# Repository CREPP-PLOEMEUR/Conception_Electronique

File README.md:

# Conception_Electronique
Le répertoire avec les sources de l'atelier Conception Electronique

## Installation de Kicad

La version de Kicad sera la version 8.X : 

## Projets 2024-2025

Pour cette année, les projets souhaités sont :

- Une station météo
- Une carte de développement pour microcontrôleur 

- Cahier des charges
- Schématique
- Commande de matériel
- Affectation des empreintes
- Routage
- Génération du dossier de fabrication
- Montage
- Debug

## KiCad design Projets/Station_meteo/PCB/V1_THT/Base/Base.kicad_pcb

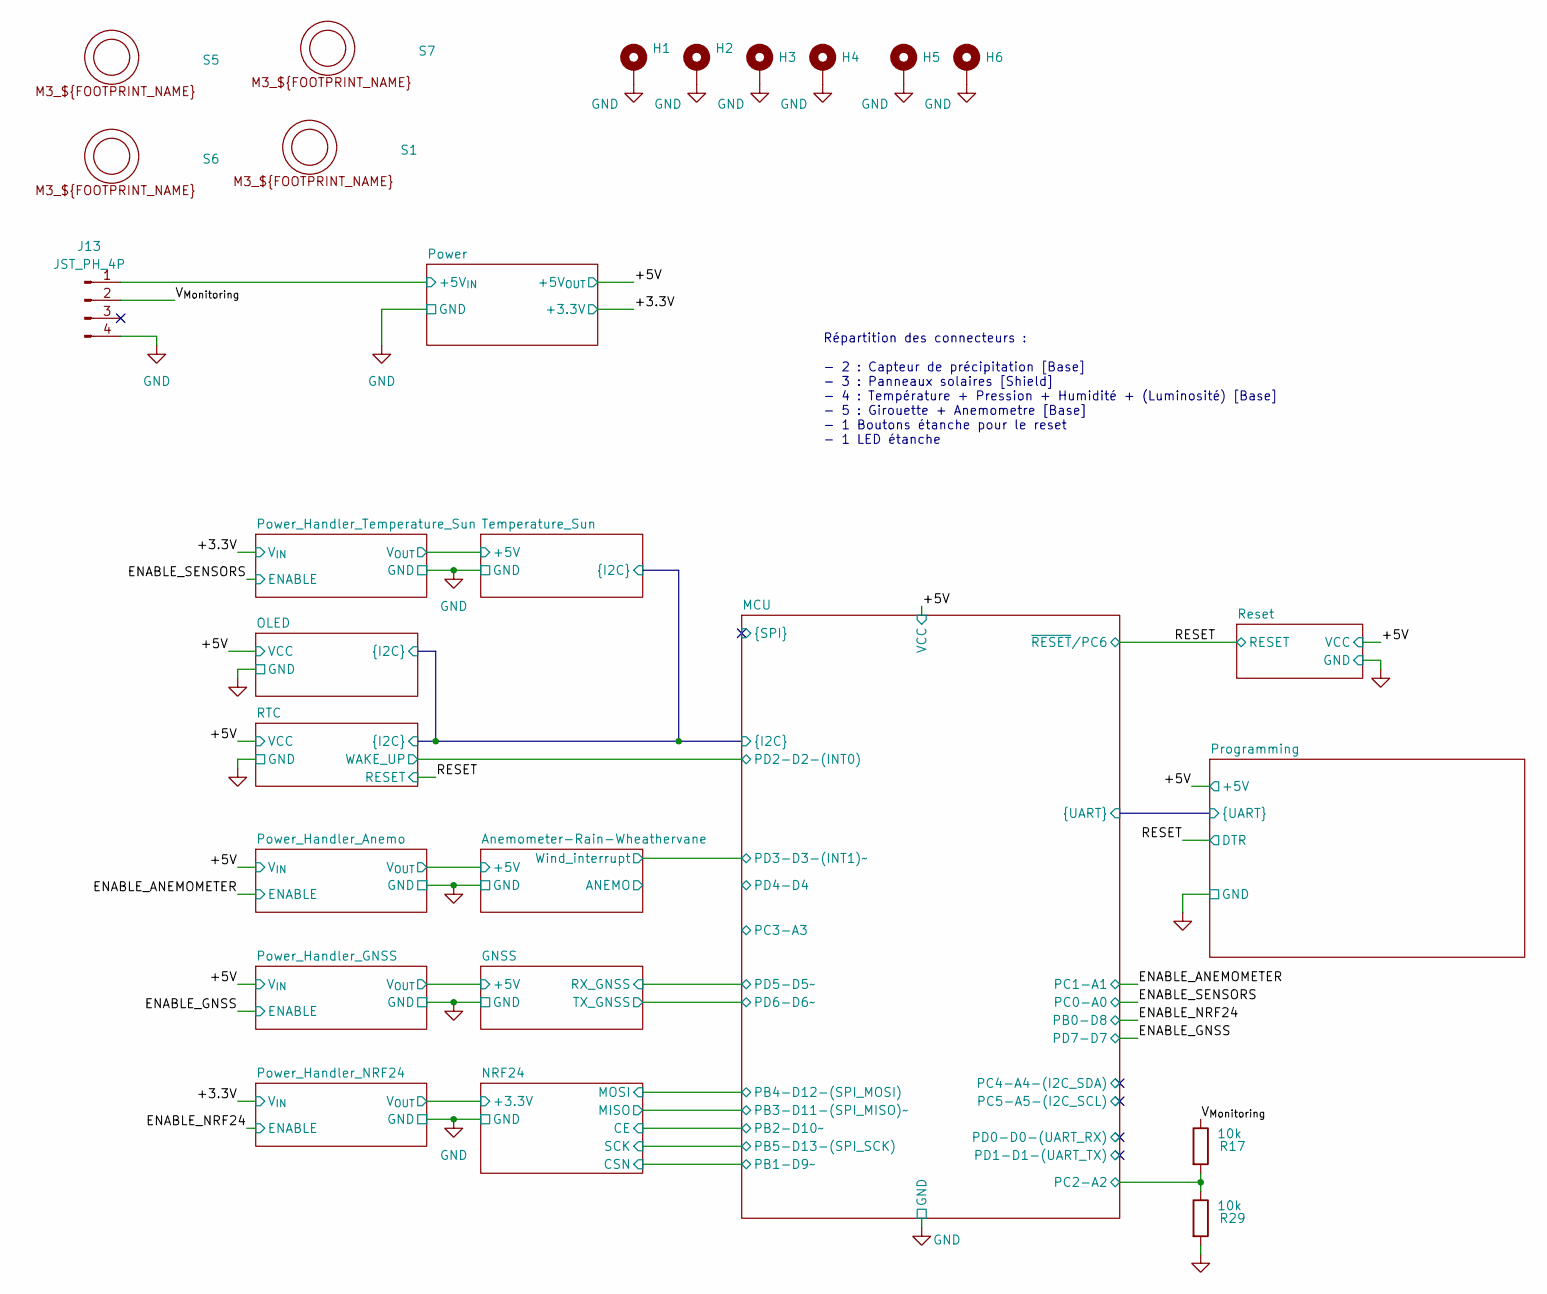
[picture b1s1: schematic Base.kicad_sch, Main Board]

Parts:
H1, H2, H3, H4, H5, H6: MountingHole_Pad; MountingHole_3.2mm_M3
J13: JST_PH_4P; JST_PH_B4B-PH-K_1x04_P2.00mm_Vertical
R17, R29: 10k; R_Axial_DIN0207_L6.3mm_D2.5mm_P7.62mm_Horizontal
S1, S5, S6, S7: Spacer_M3_MF_05mm

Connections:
/MCU/PC2-A2: R17.2, R29.1; also elsewhere on the board
/Power/+5V_{IN}: J13.1; also elsewhere on the board
/V_{Monitoring}: J13.2, R17.1
GND: H1.1, H2.1, H3.1, H4.1, H5.1, H6.1, J13.4, R29.2; also elsewhere on the board

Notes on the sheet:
Répartition des connecteurs : - 2 : Capteur de précipitation [Base] - 3 : Panneaux solaires [Shield] - 4 : Température + Pression + Humidité + (Luminosité) [Base] - 5 : Girouette + Anemometre [Base] - 1 Boutons étanche pour le reset - 1 LED étanche

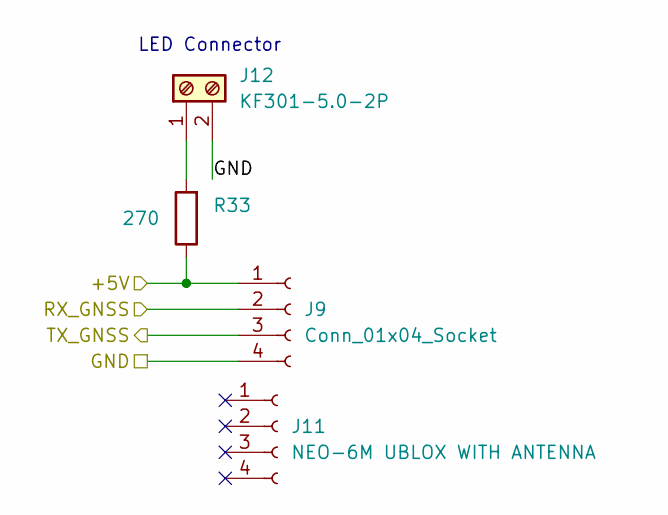
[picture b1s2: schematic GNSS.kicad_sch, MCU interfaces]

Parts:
J9: Conn_01x04_Socket; PinSocket_1x04_P2.54mm_Vertical
J11: NEO-6M UBLOX WITH ANTENNA; PinSocket_1x04_P2.54mm_Vertical
J12: KF301-5.0-2P; TerminalBlock_Phoenix_MKDS-1,5-2_1x02_P5.00mm_Horizontal
R33: 270; R_Axial_DIN0207_L6.3mm_D2.5mm_P7.62mm_Horizontal

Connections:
/GNSS/+5V: J9.1, R33.1; also elsewhere on the board
/GNSS/RX_GNSS: J9.2; also elsewhere on the board
/GNSS/TX_GNSS: J9.3; also elsewhere on the board
GND: J9.4, J12.2; also elsewhere on the board
unnamed: J12.1, R33.2

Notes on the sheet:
LED Connector

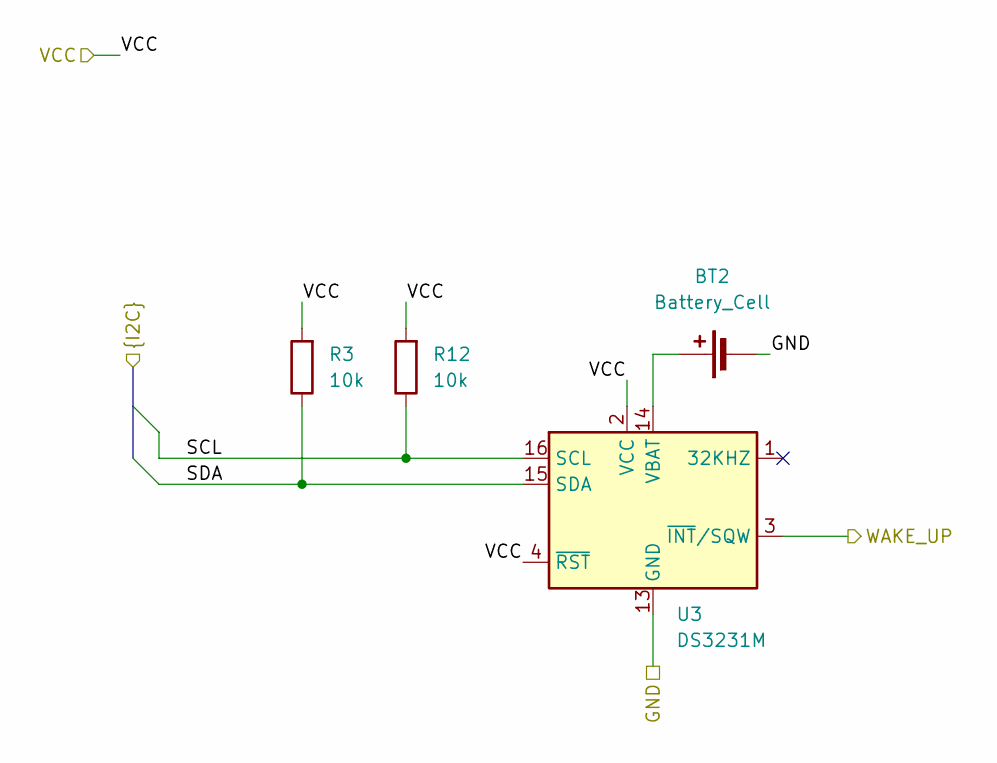
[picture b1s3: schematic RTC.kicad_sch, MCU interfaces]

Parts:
BT2: Battery_Cell; MPD_BC501SM-TR
R3, R12: 10k; R_Axial_DIN0207_L6.3mm_D2.5mm_P7.62mm_Horizontal
U3: DS3231M; SOIC-16W_7.5x10.3mm_P1.27mm

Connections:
/MCU/PD2-D2-(INT0): U3.3 (~INT/SQW); also elsewhere on the board
/MCU/SCL: R12.1, U3.16 (SCL); also elsewhere on the board
/MCU/SDA: R3.1, U3.15 (SDA); also elsewhere on the board
GND: U3.5 (GND), U3.6 (GND), U3.7 (GND), U3.8 (GND), U3.9 (GND), U3.10 (GND), U3.11 (GND), U3.12 (GND), U3.13 (GND); also elsewhere on the board
unnamed: BT2.1 (+), U3.14 (VBAT)
unnamed 75: R3.1; also elsewhere on the board
unnamed 76: R12.1; also elsewhere on the board
unnamed 77: R3.2, R12.2; also elsewhere on the board

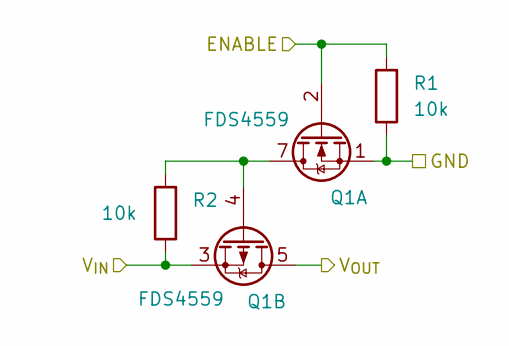
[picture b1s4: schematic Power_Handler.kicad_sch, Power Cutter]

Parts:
Q1: FDS4559; SOIC-8_3.9x4.9mm_P1.27mm
R1, R2: 10k; R_Axial_DIN0207_L6.3mm_D2.5mm_P7.62mm_Horizontal

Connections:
/Anemometer-Rain-Wheathervane/+5V: Q1.5 (D), Q1.6 (D); also elsewhere on the board
/ENABLE_ANEMOMETER: Q1.2 (G), R1.2; also elsewhere on the board
GND: Q1.1 (S), R1.1; also elsewhere on the board
unnamed: Q1.4 (G), Q1.7 (D), Q1.8 (D), R2.2

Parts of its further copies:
Q2, Q3, Q4: FDS4559; SOIC-8_3.9x4.9mm_P1.27mm
R14, R15, R16, R18, R19, R28: 10k; R_Axial_DIN0207_L6.3mm_D2.5mm_P7.62mm_Horizontal

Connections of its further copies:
/+3.3V: Q2.3 (1), Q4.3 (1), R18.1, R28.1; also elsewhere on the board
/ENABLE_GNSS: Q3.2 (G), R15.2; also elsewhere on the board
/ENABLE_NRF24: Q2.2 (G), R14.2; also elsewhere on the board
/ENABLE_SENSORS: Q4.2 (G), R16.2; also elsewhere on the board
/GNSS/+5V: Q3.5 (D), Q3.6 (D); also elsewhere on the board
/NRF24/+3.3V: Q2.5 (D), Q2.6 (D); also elsewhere on the board
/Power_Handler_Temperature_Sun/V_{OUT}: Q4.5 (D), Q4.6 (D)
GND: Q2.1 (S), Q3.1 (S), Q4.1 (S), R14.1, R15.1, R16.1; also elsewhere on the board
unnamed: Q2.4 (G), Q2.7 (D), Q2.8 (D), R18.2
unnamed: Q3.4 (G), Q3.7 (D), Q3.8 (D), R19.2
unnamed: Q4.4 (G), Q4.7 (D), Q4.8 (D), R28.2

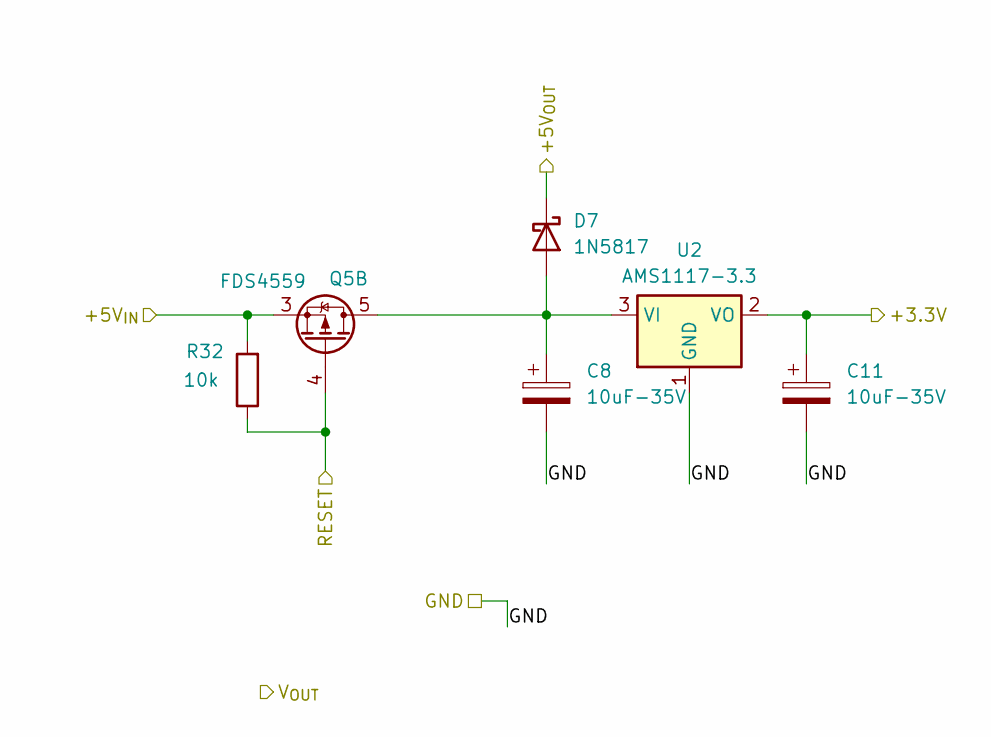
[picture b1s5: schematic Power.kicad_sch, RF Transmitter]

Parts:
C8, C11: 10uF-35V; C_Radial_D5.0mm_H11.0mm_P2.00mm
D7: 1N5817; D_DO-41_SOD81_P10.16mm_Horizontal
Q5: FDS4559; SOIC-8_3.9x4.9mm_P1.27mm
R32: 10k; R_Axial_DIN0207_L6.3mm_D2.5mm_P7.62mm_Horizontal
U2: AMS1117-3.3; SOT-223-3_TabPin2

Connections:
/+3.3V: C11.1, U2.2 (VO); also elsewhere on the board
/Power/+5V_{IN}: Q5.3 (1), R32.2; also elsewhere on the board
/Power/RESET: Q5.4 (G), R32.1
GND: C8.2, C11.2, U2.1 (GND); also elsewhere on the board
unnamed: C8.1, D7.2 (A), Q5.5 (D), Q5.6 (D), U2.3 (VI)

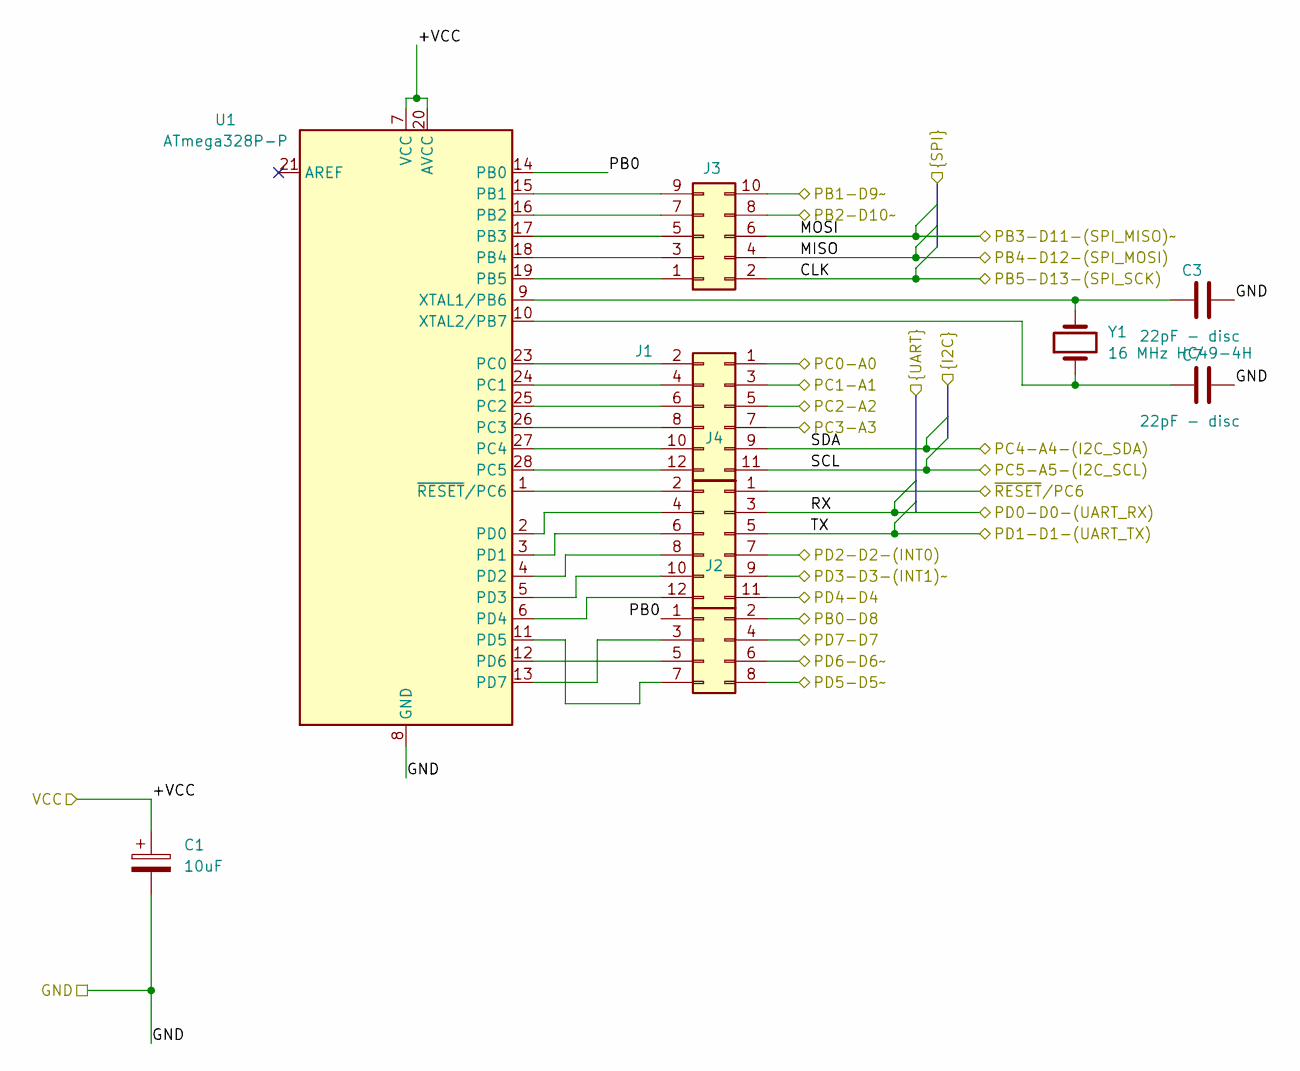
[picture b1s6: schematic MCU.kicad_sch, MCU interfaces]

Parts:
C1: 10uF; C_Radial_D5.0mm_H11.0mm_P2.00mm
C3, C7: 22pF - disc; C_Disc_D4.3mm_W1.9mm_P5.00mm
J1: Conn_02x05_Odd_Even; PinHeader_2x05_P2.54mm_Vertical
J2: Conn_02x04_Odd_Even; PinHeader_2x04_P2.54mm_Vertical
J3, J4: Conn_02x06_Odd_Even; PinHeader_2x06_P2.54mm_Vertical
U1: ATmega328P-P; DIP-28_W7.62mm_Socket
Y1: 16 MHz HC49-4H; Crystal_HC49-4H_Vertical

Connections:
/Anemometer-Rain-Wheathervane/Wind_interrupt: J4.9; also elsewhere on the board
/ENABLE_ANEMOMETER: J3.3; also elsewhere on the board
/ENABLE_GNSS: J2.4; also elsewhere on the board
/ENABLE_NRF24: J2.2; also elsewhere on the board
/ENABLE_SENSORS: J3.1; also elsewhere on the board
/GNSS/RX_GNSS: J2.8; also elsewhere on the board
/GNSS/TX_GNSS: J2.6; also elsewhere on the board
/MCU/CLK: J1.2; also elsewhere on the board
/MCU/MISO: J1.4; also elsewhere on the board
/MCU/MOSI: J1.6; also elsewhere on the board
/MCU/PB0: J2.1, U1.14 (PB0)
/MCU/PB1-D9~: J1.10; also elsewhere on the board
/MCU/PB2-D10~: J1.8; also elsewhere on the board
/MCU/PC2-A2: J3.5; also elsewhere on the board
/MCU/PC3-A3: J3.7
/MCU/PD2-D2-(INT0): J4.7; also elsewhere on the board
/MCU/PD4-D4: J4.11
/MCU/RX: J4.3; also elsewhere on the board
/MCU/SCL: J3.11; also elsewhere on the board
/MCU/SDA: J3.9; also elsewhere on the board
/MCU/TX: J4.5; also elsewhere on the board
GND: C1.2, C3.2, C7.2, U1.8 (GND), U1.22 (GND); also elsewhere on the board
unnamed: J1.1, U1.19 (PB5)
unnamed: J1.3, U1.18 (PB4)
unnamed: J1.5, U1.17 (PB3)
unnamed: J1.7, U1.16 (PB2)
unnamed: J1.9, U1.15 (PB1)
unnamed: J2.3, U1.13 (PD7)
unnamed: J2.5, U1.12 (PD6)
unnamed: J2.7, U1.11 (PD5)
unnamed: J3.2, U1.23 (PC0)
unnamed: J3.4, U1.24 (PC1)
unnamed: J3.6, U1.25 (PC2)
unnamed: J3.8, U1.26 (PC3)
unnamed: J3.10, U1.27 (PC4)
unnamed: J3.12, U1.28 (PC5)
unnamed: J4.2, U1.1 (~RESET/PC6)
unnamed: J4.4, U1.2 (PD0)
unnamed: J4.6, U1.3 (PD1)
unnamed: J4.8, U1.4 (PD2)
unnamed: J4.10, U1.5 (PD3)
unnamed: J4.12, U1.6 (PD4)
unnamed: C3.1, U1.9 (XTAL1/PB6), Y1.2
unnamed: C7.1, U1.10 (XTAL2/PB7), Y1.1

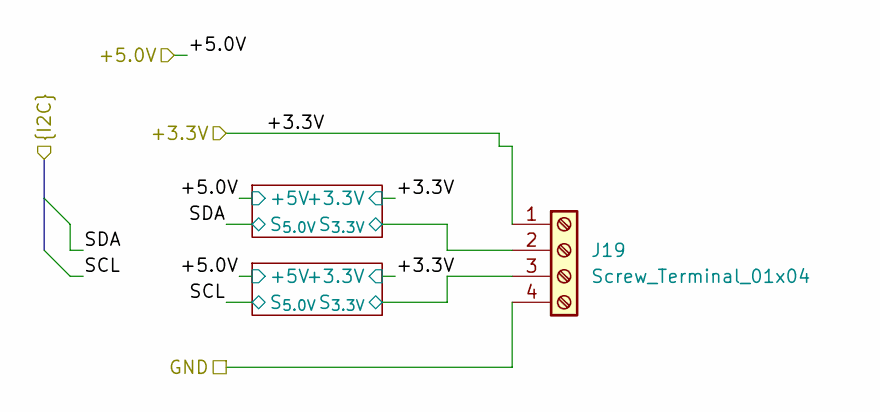
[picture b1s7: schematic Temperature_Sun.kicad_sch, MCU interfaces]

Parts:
J19: Screw_Terminal_01x04; TerminalBlock_Phoenix_MKDS-1,5-4-5.08_1x04_P5.08mm_Horizont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

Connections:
/Temperature_Sun/+3.3V: J19.1; also elsewhere on the board
/Temperature_Sun/Translator1/S_{3.3V}: J19.3; also elsewhere on the board
/Temperature_Sun/Translator/S_{3.3V}: J19.2; also elsewhere on the board
GND: J19.4; also elsewhere on the board

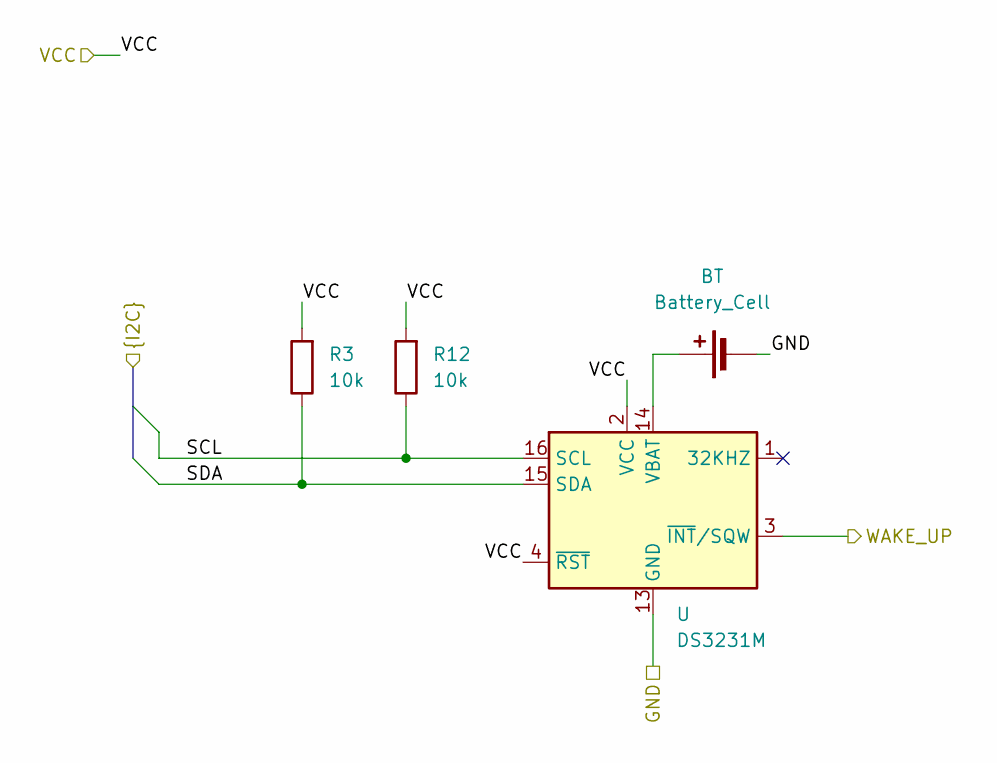
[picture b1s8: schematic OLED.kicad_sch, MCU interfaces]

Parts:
BT: Battery_Cell; MPD_BC501SM-TR
R3, R12: 10k; R_Axial_DIN0207_L6.3mm_D2.5mm_P7.62mm_Horizontal
U: DS3231M; SOIC-16W_7.5x10.3mm_P1.27mm

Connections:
/MCU/SCL: R12.1; also elsewhere on the board
/MCU/SDA: R3.1; also elsewhere on the board
unnamed: BT.1 (+), U.14 (VBAT)
unnamed: R3.1, U.15 (SDA)
unnamed: R12.1, U.16 (SCL)
unnamed: R3.2, R12.2, U.2 (VCC), U.4 (~RST)
unnamed: U.5 (GND), U.6 (GND), U.7 (GND), U.8 (GND), U.9 (GND), U.10 (GND), U.11 (GND), U.12 (GND), U.13 (GND)

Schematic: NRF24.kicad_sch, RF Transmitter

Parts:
U8: NRF24L01_Breakout; nRF24L01_Breakout

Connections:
/MCU/MOSI: U8.7 (MISO); also elsewhere on the board
/NRF24/+3.3V: U8.2 (VCC); also elsewhere on the board
/NRF24/Bridge1/OUT: U8.6 (MOSI); also elsewhere on the board
/NRF24/Bridge2/OUT: U8.4 (~CSN); also elsewhere on the board
/NRF24/Bridge3/OUT: U8.3 (CE); also elsewhere on the board
/NRF24/Bridge/OUT: U8.5 (SCK); also elsewhere on the board
GND: U8.1 (GND); also elsewhere on the board

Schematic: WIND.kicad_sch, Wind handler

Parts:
C4, C6: 100nF; C_0603_1608Metric
C5: 10uF; C_Radial_D5.0mm_H11.0mm_P2.00mm
D1: LED; LED_D3.0mm
D8: 1N5817; D_DO-41_SOD81_P10.16mm_Horizontal
J5: KF301-5.0-2P; TerminalBlock_Phoenix_MKDS-1,5-2_1x02_P5.00mm_Horizontal
J6: Conn_01x03_Pin; PinHeader_1x03_P2.54mm_Vertical
J20: Screw_Terminal_01x04; TerminalBlock_Phoenix_MKDS-1,5-4-5.08_1x04_P5.08mm_Horizont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
JP2: Jumper; PinHeader_1x02_P2.54mm_Vertical
JP3: Jumper_2.54mm_blue
R4: R_10K_SMD_0603; R_0603_1608Metric
R5, R11: 100k; R_Axial_DIN0207_L6.3mm_D2.5mm_P7.62mm_Horizontal
R6, R7, R8, R10: 10k; R_Axial_DIN0207_L6.3mm_D2.5mm_P7.62mm_Horizontal
R9: 270; R_Axial_DIN0207_L6.3mm_D2.5mm_P7.62mm_Horizontal
RV1: R_Potentiometer; Potentiometer_Bourns_3266Y_Vertical
T9, T10, T11: TP; TestPoint_Pad_D1.0mm
U4: LM358; DIP-8_W7.62mm
U5: 74HC123; DIP-16_W7.62mm_Socket

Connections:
/Anemometer-Rain-Wheathervane/+5V: C5.1, R4.1, R5.1, RV1.1, U4.8 (V+), U5.16 (VCC); also elsewhere on the board
/Anemometer-Rain-Wheathervane/Anemo_{signal}: J6.2, T9.1, U5.9 (A)
/Anemometer-Rain-Wheathervane/Wind_interrupt: JP2.1 (A), R7.2, R8.2, U4.7; also elsewhere on the board
GND: C5.2, C6.2, R8.1, R9.2, R11.2, RV1.3, U4.4 (V-), U5.8 (GND), U5.10 (B), U5.11 (Clr); also elsewhere on the board
unnamed: D1.2 (A), JP2.2 (B)
unnamed: D1.1 (K), R9.1
unnamed: J5.1, J6.3, R11.1
unnamed: J5.2, J6.1, R5.2
unnamed: C6.1, R10.2, U4.3 (+)
unnamed: R6.1, T11.1, U4.1, U4.2 (-)
unnamed: R6.2, R7.1, U4.5 (+)
unnamed: RV1.2, U4.6 (-)
unnamed: C4.2, U5.6 (Cext)
unnamed: R10.1, T10.1, U5.5 (Q)
unnamed: C4.1, R4.2, U5.7 (RCext)

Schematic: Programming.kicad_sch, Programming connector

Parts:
C2, C19: 100nF; C_0603_1608Metric
D10: 1N5817; D_DO-41_SOD81_P10.16mm_Horizontal
J8: USB_C_Receptacle; USB_C_Receptacle_GCT_USB4085
J15, J16: SolderJumper_2_Bridged; SolderJumper-2_P1.3mm_Bridged_Pad1.0x1.5mm
U10: CH340G; SOIC-16_3.9x9.9mm_P1.27mm
Y2: Crystal HC49-4H 12 MHz; Crystal_HC49-4H_Vertical

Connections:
/MCU/RX: J15.2 (B); also elsewhere on the board
/MCU/TX: J16.2 (B); also elsewhere on the board
/Programming/D+: J8.A6 (D+), J8.B6 (D+), U10.5 (UD+)
/Programming/D-: J8.A7 (D-), J8.B7 (D-), U10.6 (UD-)
GND: C2.2, J8.A1 (GND), J8.A12 (GND), J8.B1 (GND), J8.B12 (GND), U10.1 (GND); also elsewhere on the board
unnamed: J15.1 (A), U10.2 (TXD)
unnamed: J16.1 (A), U10.3 (RXD)
unnamed: C2.1, U10.4 (V3)
unnamed: U10.7 (XI), Y2.2
unnamed: U10.8 (XO), Y2.1
unnamed: C19.1, U10.13 (~DTR)

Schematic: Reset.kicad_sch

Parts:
R13: 10k; R_Axial_DIN0207_L6.3mm_D2.5mm_P7.62mm_Horizontal
SW1: SW_B; SW_PUSH_6mm_H8mm

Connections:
GND: SW1.1 (A); also elsewhere on the board

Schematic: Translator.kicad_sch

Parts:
R20, R21: 10k; R_Axial_DIN0207_L6.3mm_D2.5mm_P7.62mm_Horizontal

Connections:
/MCU/MISO: R20.1; also elsewhere on the board
/NRF24/Bridge1/OUT: R20.2, R21.1; also elsewhere on the board
GND: R21.2; also elsewhere on the board

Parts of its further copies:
R22, R23, R24, R25, R26, R27, R34, R35: 10k; R_Axial_DIN0207_L6.3mm_D2.5mm_P7.62mm_Horizontal

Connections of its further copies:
/MCU/CLK: R22.1; also elsewhere on the board
/MCU/PB1-D9~: R24.1; also elsewhere on the board
/MCU/PB2-D10~: R26.1; also elsewhere on the board
/MCU/SDA: R34.2; also elsewhere on the board
/NRF24/Bridge2/OUT: R24.2, R25.1; also elsewhere on the board
/NRF24/Bridge3/OUT: R26.2, R27.1; also elsewhere on the board
/NRF24/Bridge/OUT: R22.2, R23.1; also elsewhere on the board
/Temperature_Sun/+3.3V: R35.1; also elsewhere on the board
/Temperature_Sun/+5.0V: R34.1; also elsewhere on the board
/Temperature_Sun/Translator/S_{3.3V}: R35.2; also elsewhere on the board
GND: R23.2, R25.2, R27.2; also elsewhere on the board

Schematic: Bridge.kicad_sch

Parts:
R20, R21: 10k; R_Axial_DIN0207_L6.3mm_D2.5mm_P7.62mm_Horizontal

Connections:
/MCU/MISO: R20.1; also elsewhere on the board
/NRF24/Bridge1/OUT: R20.2, R21.1; also elsewhere on the board
GND: R21.2; also elsewhere on the board

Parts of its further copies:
R22, R23, R24, R25, R26, R27: 10k; R_Axial_DIN0207_L6.3mm_D2.5mm_P7.62mm_Horizontal

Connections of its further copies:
/MCU/CLK: R22.1; also elsewhere on the board
/MCU/PB1-D9~: R24.1; also elsewhere on the board
/MCU/PB2-D10~: R26.1; also elsewhere on the board
/NRF24/Bridge2/OUT: R24.2, R25.1; also elsewhere on the board
/NRF24/Bridge3/OUT: R26.2, R27.1; also elsewhere on the board
/NRF24/Bridge/OUT: R22.2, R23.1; also elsewhere on the board
GND: R23.2, R25.2, R27.2; also elsewhere on the board

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
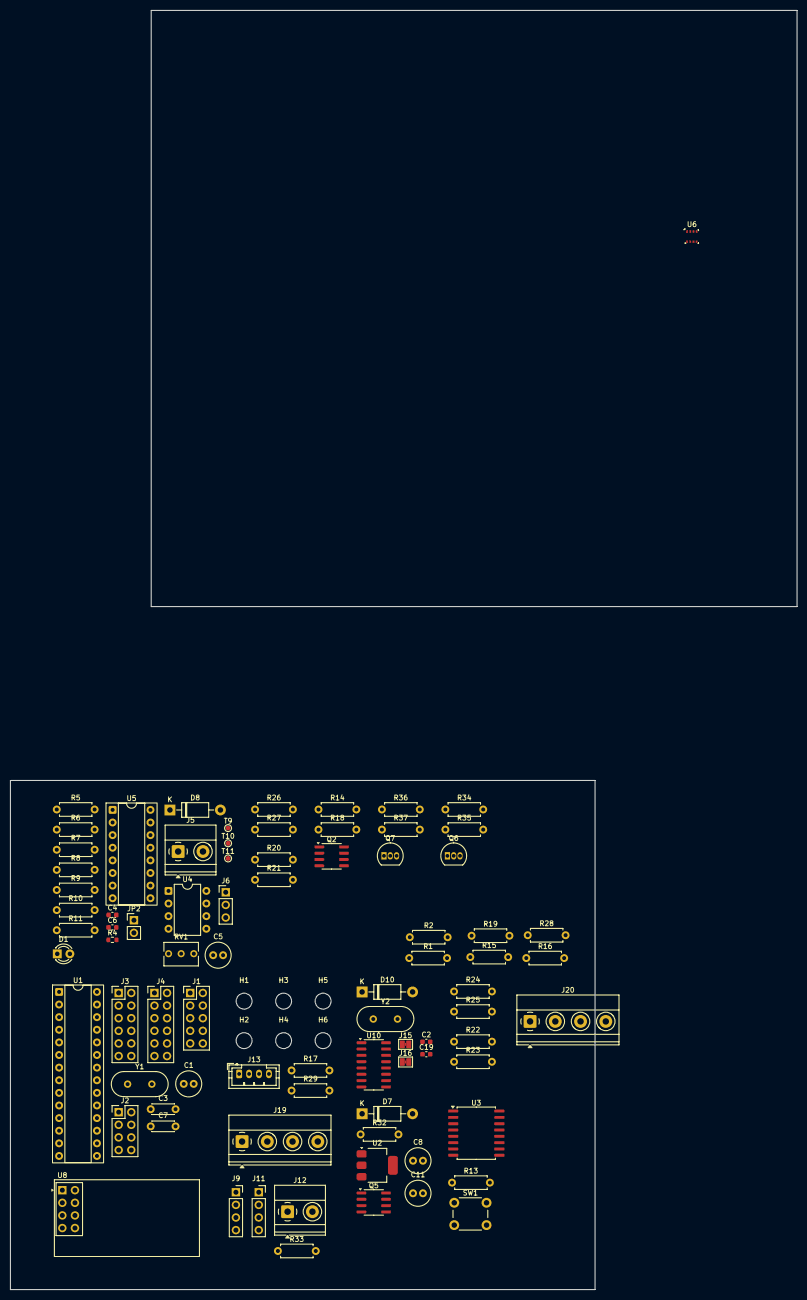
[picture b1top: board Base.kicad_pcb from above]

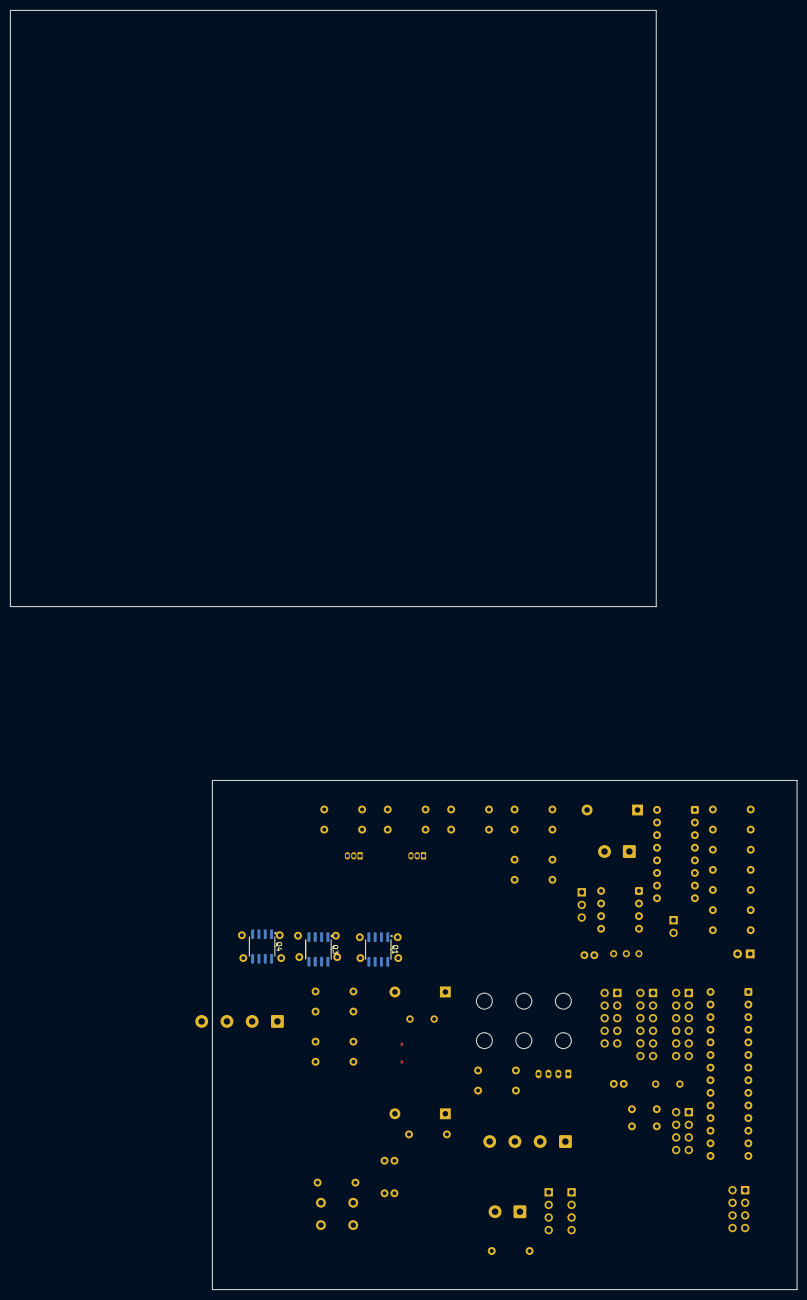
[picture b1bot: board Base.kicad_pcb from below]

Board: 2 copper layers, 158.3 x 257.5 mm, 96 parts (3 on the bottom side), 84 nets.

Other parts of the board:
Q6, Q7: 2N7000; TO-92_Inline
R36, R37: 10k; R_Axial_DIN0207_L6.3mm_D2.5mm_P7.62mm_Horizontal
STACKUP1: (no value)
U6: BME280; Bosch_LGA-8_2.5x2.5mm_P0.65mm_ClockwisePinNumbering

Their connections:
/MCU/SCL: Q7.3 (D), R37.2; also elsewhere on the board
/MCU/SDA: Q6.3 (D); also elsewhere on the board
/Temperature_Sun/+3.3V: Q6.2 (G), Q7.2 (G), R36.1; also elsewhere on the board
/Temperature_Sun/+5.0V: R37.1; also elsewhere on the board
/Temperature_Sun/Translator1/S_{3.3V}: Q7.1 (S), R36.2; also elsewhere on the board
/Temperature_Sun/Translator/S_{3.3V}: Q6.1 (S); also elsewhere on the board
